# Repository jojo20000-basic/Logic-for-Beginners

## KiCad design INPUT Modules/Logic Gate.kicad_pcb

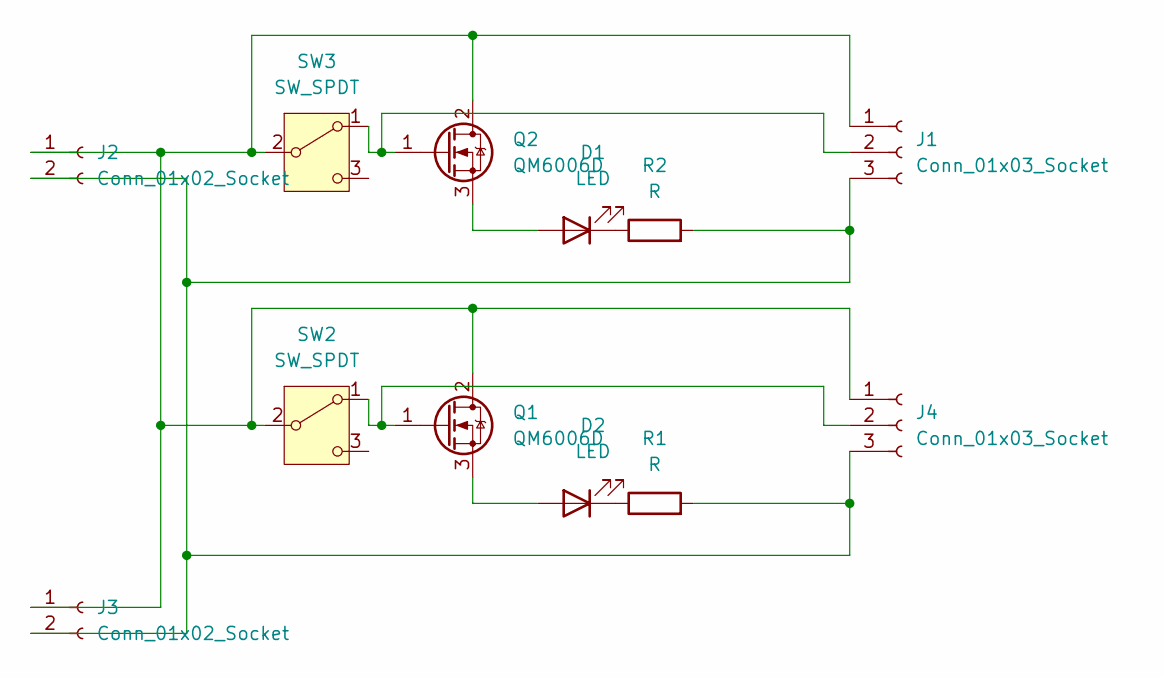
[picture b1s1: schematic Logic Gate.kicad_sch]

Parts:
D1, D2: LED; LED_1206_3216Metric
J1, J4: Conn_01x03_Socket; PinSocket_1x03_P2.54mm_Horizontal
J2, J3: Conn_01x02_Socket; PinSocket_1x02_P2.54mm_Horizontal
Q1, Q2: QM6006D; TO-252-2
R1, R2: R; R_1206_3216Metric
SW2, SW3: SW_SPDT; SW_Slide-03_Wuerth-WS-SLTV_10x2.5x6.4_P2.54mm

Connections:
unnamed: D1.2 (A), Q2.3 (S)
unnamed: D1.1 (K), R2.1
unnamed: D2.2 (A), Q1.3 (S)
unnamed: D2.1 (K), R1.1
unnamed: J1.1, J2.1, J3.1, J4.1, Q1.2 (D), Q2.2 (D), SW2.2 (B), SW3.2 (B)
unnamed: J1.2, Q2.1 (G), SW3.1 (A)
unnamed: J1.3, J2.2, J3.2, J4.3, R1.2, R2.2
unnamed: J4.2, Q1.1 (G), SW2.1 (A)

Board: 2 copper layers, 12 parts (4 on the bottom side), 8 nets, no tracks yet.

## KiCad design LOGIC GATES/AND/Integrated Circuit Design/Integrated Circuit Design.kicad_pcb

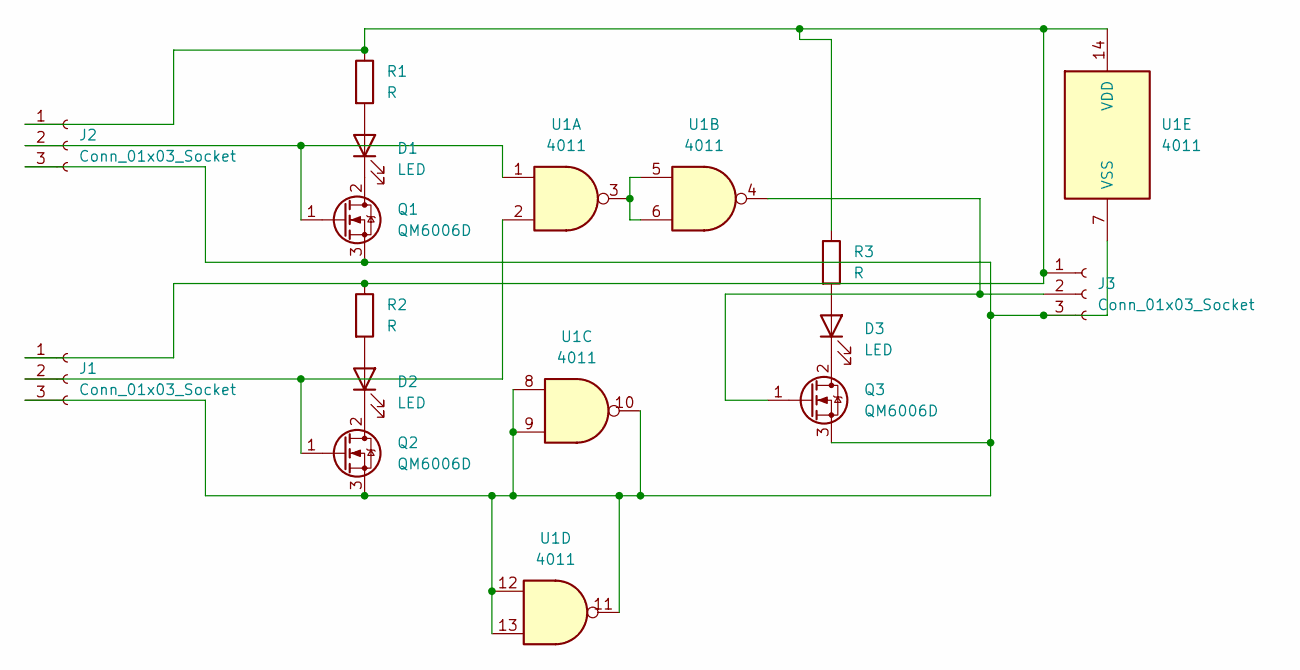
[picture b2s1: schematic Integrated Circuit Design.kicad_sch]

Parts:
D1, D2, D3: LED; LED_1206_3216Metric
J1, J2, J3: Conn_01x03_Socket; PinSocket_1x03_P2.54mm_Horizontal
Q1, Q2, Q3: QM6006D; TO-252-2
R1, R2, R3: R; R_1206_3216Metric
U1: 4011; DIP-14_W7.62mm_Socket

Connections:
unnamed: D1.2 (A), R1.2
unnamed: D1.1 (K), Q1.2 (D)
unnamed: D2.2 (A), R2.2
unnamed: D2.1 (K), Q2.2 (D)
unnamed: D3.2 (A), R3.2
unnamed: D3.1 (K), Q3.2 (D)
unnamed: J1.1, J2.1, J3.1, R1.1, R2.1, R3.1, U1.14 (VDD)
unnamed: J1.2, Q2.1 (G), U1.2
unnamed: J1.3, J2.3, J3.3, Q1.3 (S), Q2.3 (S), Q3.3 (S), U1.7 (VSS), U1.8, U1.9, U1.10, U1.11, U1.12, U1.13
unnamed: J2.2, Q1.1 (G), U1.1
unnamed: J3.2, Q3.1 (G), U1.4
unnamed: U1.3, U1.5, U1.6

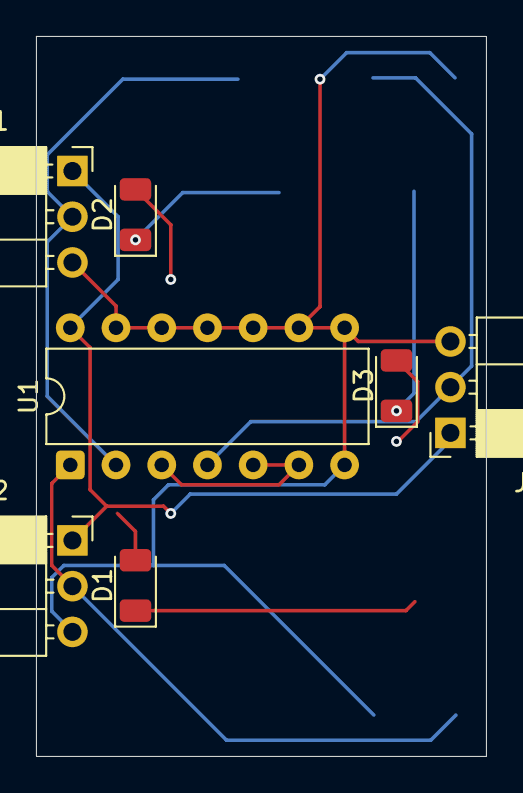
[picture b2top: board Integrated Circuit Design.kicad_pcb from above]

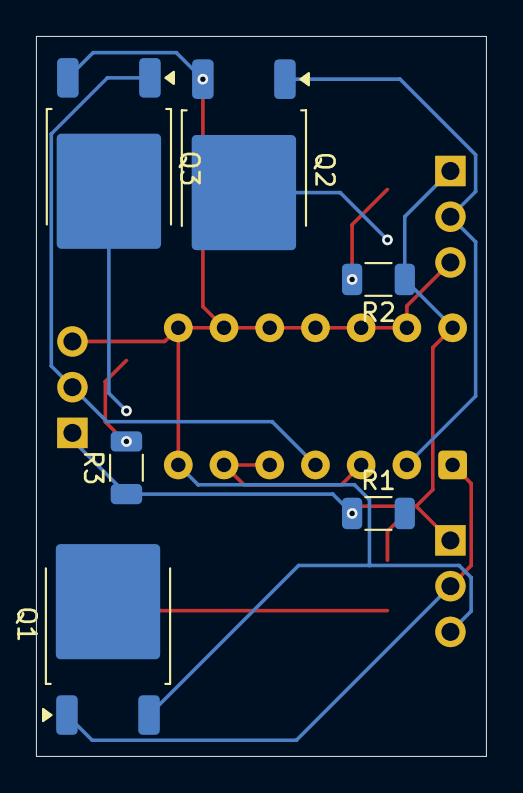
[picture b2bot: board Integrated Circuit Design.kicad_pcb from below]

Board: 2 copper layers, 25.0 x 40.0 mm, 13 parts (6 on the bottom side), 12 nets.

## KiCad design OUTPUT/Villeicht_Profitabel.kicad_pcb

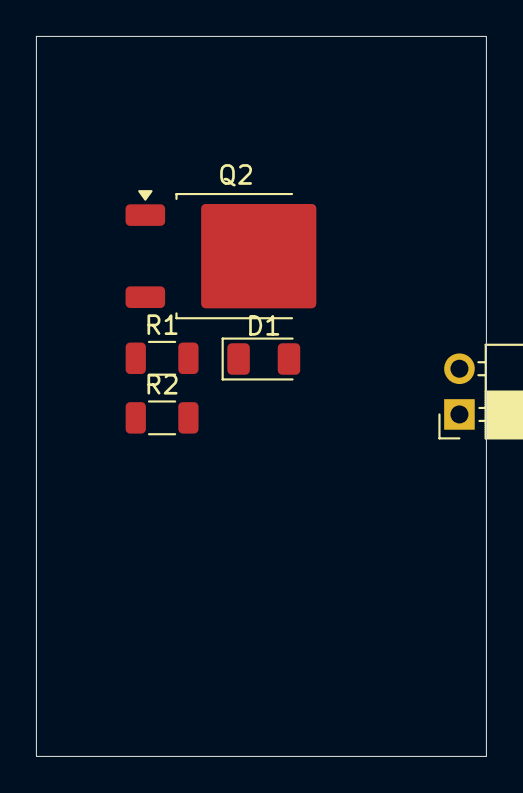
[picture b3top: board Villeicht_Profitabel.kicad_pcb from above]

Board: 2 copper layers, 25.0 x 40.0 mm, 5 parts (0 on the bottom side), 5 nets, no tracks yet.

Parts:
D1: LED; LED_1206_3216Metric
J1: Conn_01x03_Pin; PinSocket_1x02_P2.54mm_Horizontal
Q2: QM6006D; TO-252-2
R1: R; R_1206_3216Metric
R2: 1k; R_1206_3216Metric

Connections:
unnamed: D1.2 (A), Q2.3 (S)
unnamed: D1.1 (K), R1.1
unnamed: J1.1, Q2.2 (D)
unnamed: J1.2, R2.2
unnamed: Q2.1 (G), R2.1

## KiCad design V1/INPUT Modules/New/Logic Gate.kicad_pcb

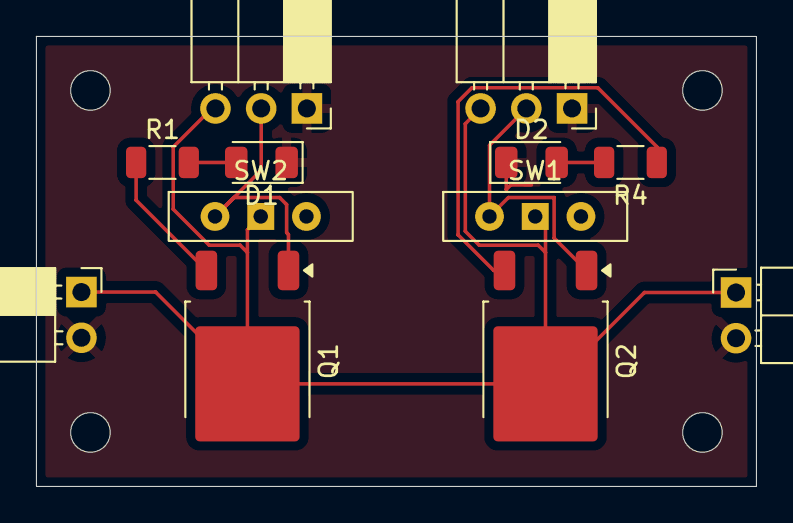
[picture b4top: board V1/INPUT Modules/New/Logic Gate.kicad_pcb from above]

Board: 2 copper layers, 40.0 x 25.0 mm, 12 parts (0 on the bottom side), 8 nets.

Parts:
D1, D2: LED; LED_1206_3216Metric
J1, J3: Conn_01x03; PinSocket_1x03_P2.54mm_Horizontal
J2: Conn_01x02; PinSocket_1x02_P2.54mm_Horizontal
J4: Conn_01x02; PinHeader_1x02_P2.54mm_Horizontal
Q1, Q2: QM6006D; TO-252-2
R1, R4: R; R_1206_3216Metric
SW1, SW2: SW_SPST; SW_Slide-03_Wuerth-WS-SLTV_10x2.5x6.4_P2.54mm

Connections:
+5V: J1.3, J2.1, J3.3, J4.1, Q1.2 (D), Q2.2 (D), SW1.1 (A), SW2.1 (A)
GND: D1.1 (K), D2.1 (K), J1.1, J2.2, J3.1, J4.2
unnamed: D1.2 (A), R1.2
unnamed: D2.2 (A), R4.2
unnamed: J1.2, Q1.1 (G), SW2.2 (B)
unnamed: J3.2, Q2.1 (G), SW1.2 (B)
unnamed: Q1.3 (S), R1.1
unnamed: Q2.3 (S), R4.1
